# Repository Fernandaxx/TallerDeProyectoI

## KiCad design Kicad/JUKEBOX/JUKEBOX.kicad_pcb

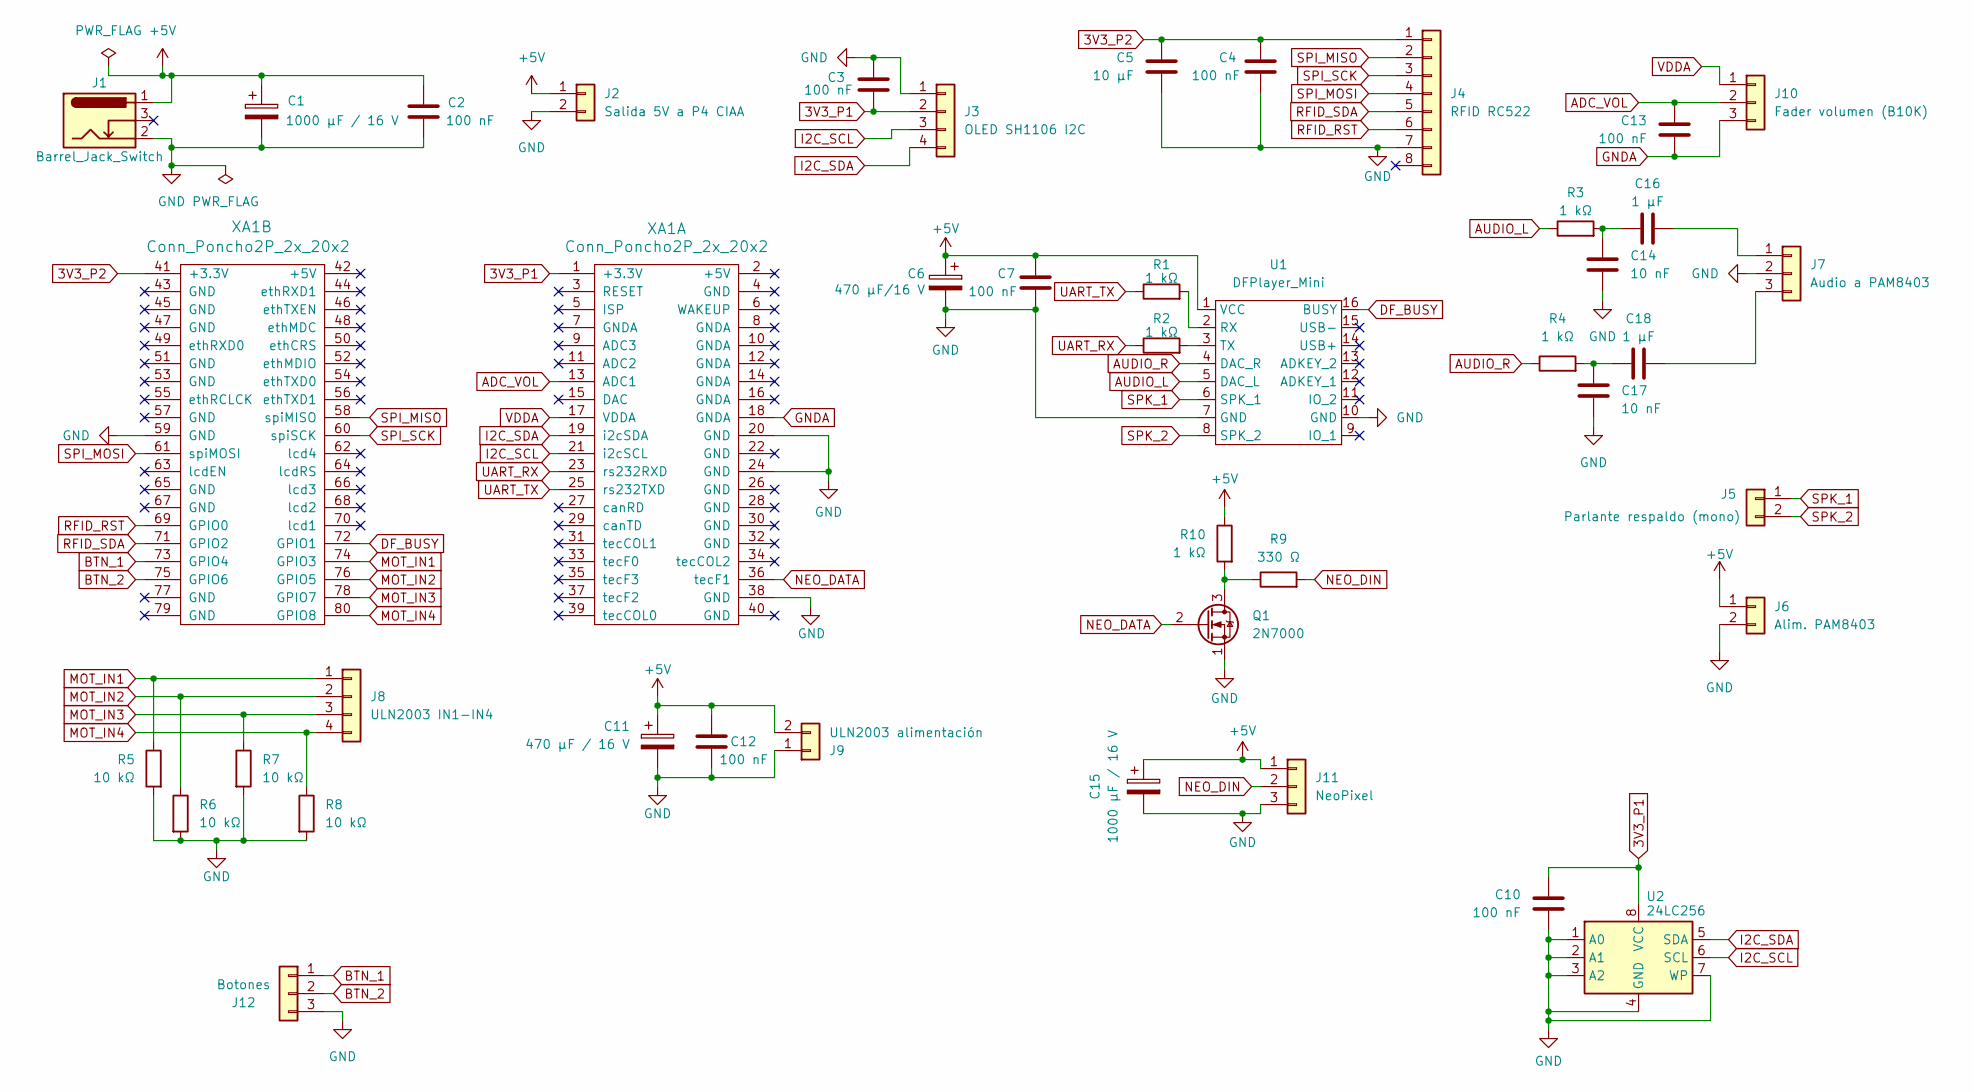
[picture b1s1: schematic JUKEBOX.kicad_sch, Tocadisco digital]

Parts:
C1, C15: 1000 µF / 16 V; CP_D10_P5.00
C2, C3, C4, C7, C10, C12, C13: 100 nF; C_Disc_D4.7_P5.00
C5: 10 µF; C_Disc_D4.7_P5.00
C6: 470 µF/16 V; CP_D8_P3.50
C11: 470 µF / 16 V; CP_D8_P3.50
C14, C17: 10 nF; C_Disc_D4.7_P5.00
C16, C18: 1 µF; C_Disc_D5_P5.00
J1: Barrel_Jack_Switch; BarrelJack_H
J2: Salida 5V a P4 CIAA; TB_P5.08_1x02
J3: OLED SH1106 I2C; PinHeader_1x04
J4: RFID RC522; PinHeader_1x08
J5: Parlante respaldo (mono); PinHeader_1x02
J6: Alim. PAM8403; PinHeader_1x02
J7: Audio a PAM8403; PinHeader_1x03
J8: ULN2003 IN1-IN4; PinHeader_1x04
J9: ULN2003 alimentación; PinHeader_1x02_Robusto
J10: Fader volumen (B10K); PinHeader_1x03
J11: NeoPixel; PinHeader_1x03
J12: Botones; PinHeader_1x03
Q1: 2N7000; TO-92_Wide
R1, R2, R3, R4, R10: 1 kΩ; R_Axial_P10.16
R5, R6, R7, R8: 10 kΩ; R_Axial_P10.16
R9: 330 Ω; R_Axial_P10.16
U1: DFPlayer_Mini
U2: 24LC256; DIP-8_Socket
XA1: Conn_Poncho2P_2x_20x2; Poncho_Grande_Reducido

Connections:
3V3_P1: C3.1, C10.1, J3.2, U2.8 (VCC), XA1.1 (+3.3V)
3V3_P2: C4.2, C5.2, J4.1, XA1.41 (+3.3V)
+5V: C1.1, C2.1, C6.1, C7.1, C11.1, C12.1, C15.1, J1.1, J2.1, J6.1, J9.2, J11.1, R10.1, U1.1 (VCC)
ADC_VOL: C13.1, J10.2, XA1.13 (ADC1)
AUDIO_L: R3.1, U1.5 (DAC_L)
AUDIO_R: R4.1, U1.4 (DAC_R)
BTN_1: J12.1, XA1.73 (GPIO4)
BTN_2: J12.2, XA1.75 (GPIO6)
DF_BUSY: U1.16 (BUSY), XA1.72 (GPIO1)
GND: C1.2, C2.2, C3.2, C4.1, C5.1, C6.2, C7.2, C10.2, C11.2, C12.2, C14.2, C15.2, C17.2, J1.2, J2.2, J3.1, J4.7, J6.2, J7.2, J9.1, J11.3, J12.3, Q1.1 (S), R5.2, R6.2, R7.2, R8.2, U1.7 (GND), U1.10 (GND), U2.1 (A0), U2.2 (A1), U2.3 (A2), U2.4 (GND), U2.7 (WP), XA1.20 (GND), XA1.24 (GND), XA1.38 (GND), XA1.59 (GND)
GNDA: C13.2, J10.3, XA1.18 (GNDA)
I2C_SCL: J3.3, U2.6 (SCL), XA1.21 (i2cSCL)
I2C_SDA: J3.4, U2.5 (SDA), XA1.19 (i2cSDA)
MOT_IN1: J8.1, R5.1, XA1.74 (GPIO3)
MOT_IN2: J8.2, R6.1, XA1.76 (GPIO5)
MOT_IN3: J8.3, R7.1, XA1.78 (GPIO7)
MOT_IN4: J8.4, R8.1, XA1.80 (GPIO8)
NEO_DATA: Q1.2 (G), XA1.36 (tecF1)
NEO_DIN: J11.2, R9.2
unnamed: C14.1, C16.1, R3.2
unnamed: C17.1, C18.1, R4.2
unnamed: C16.2, J7.1
unnamed: C18.2, J7.3
unnamed: Q1.3 (D), R9.1, R10.2
unnamed: R1.2, U1.2 (RX)
unnamed: R2.2, U1.3 (TX)
RFID_RST: J4.6, XA1.69 (GPIO0)
RFID_SDA: J4.5, XA1.71 (GPIO2)
SPI_MISO: J4.2, XA1.58 (spiMISO)
SPI_MOSI: J4.4, XA1.61 (spiMOSI)
SPI_SCK: J4.3, XA1.60 (spiSCK)
SPK_1: J5.1, U1.6 (SPK_1)
SPK_2: J5.2, U1.8 (SPK_2)
UART_RX: R2.1, XA1.23 (rs232RXD)
UART_TX: R1.1, XA1.25 (rs232TXD)
VDDA: J10.1, XA1.17 (VDDA)

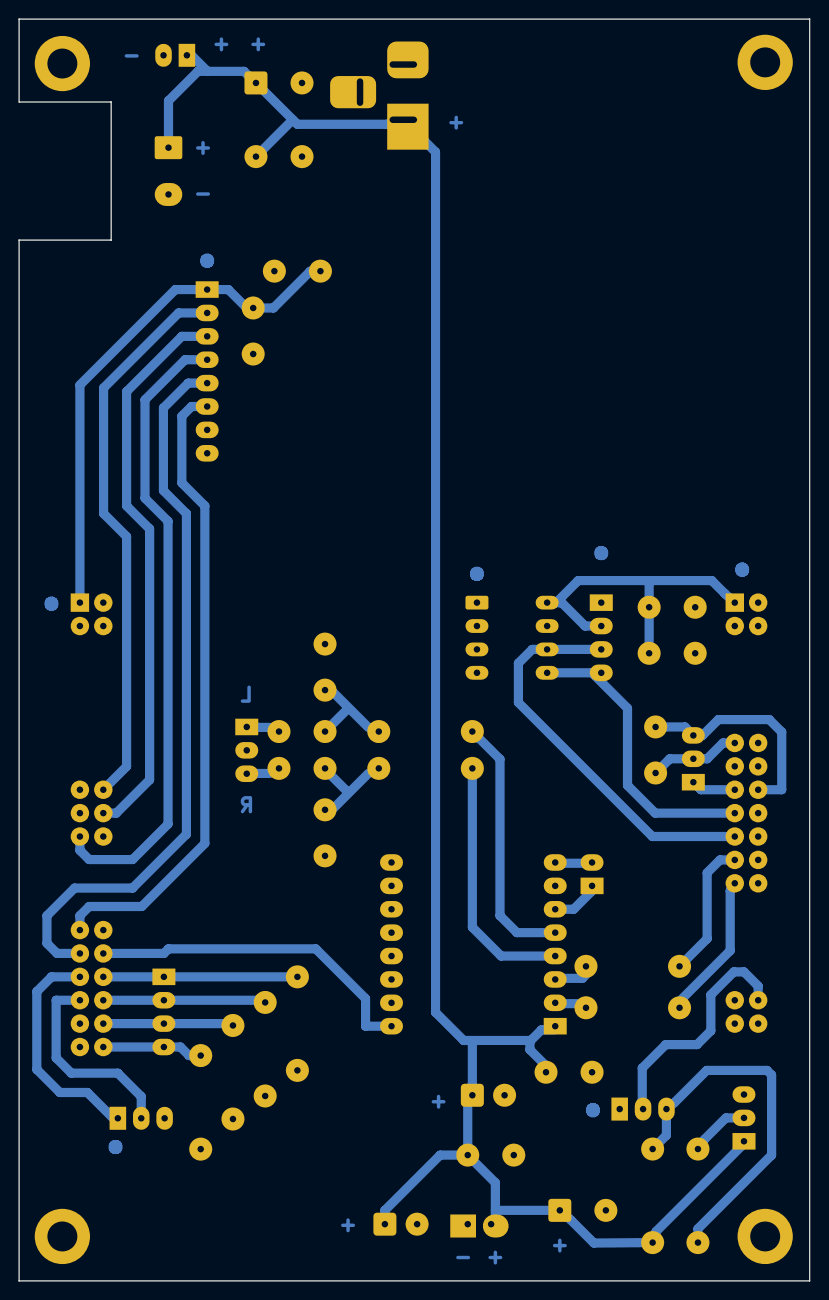
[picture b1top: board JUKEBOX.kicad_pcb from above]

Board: 2 copper layers, 85.9 x 137.0 mm, 42 parts (0 on the bottom side), 36 nets.

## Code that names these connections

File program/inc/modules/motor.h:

#ifndef MOTOR_H
#define MOTOR_H

#include "main.h"

#define MOTOR_IN1 GPIO5
#define MOTOR_IN2 GPIO6
#define MOTOR_IN3 GPIO7
#define MOTOR_IN4 GPIO8

#define MOTOR_STEPS_PER_REV 4096u // half-steps por vuelta del eje de salida (aprox.)

typedef enum { 
    MOTOR_CW,
    MOTOR_CCW
} motorDir_t;

void    tareaMotor(void);   
void    motorInit(void);   
void    motorEncender(motorDir_t dir);
void    motorApagar(void);

#endif
